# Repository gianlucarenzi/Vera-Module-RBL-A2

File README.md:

# VERA Module RBL-A2

<div align="center">

**Commander X16 graphics and sound, 256 KB of RAM disk, one Apple II slot.**

*🌐 English | [🌐 Italiano](#vera-module-rbl-a2-italiano)*

</div>

> [!WARNING]
> **v1.0 — PRE-PRODUCTION.** The PCB is routed and passes KiCad's DRC; the first boards are
> being made and are not tested yet. The firmware has been checked on the host and in an
> emulator only.

## ✨ Highlights

- 🎨 **VERA**, the Commander X16 video and audio chip, on a Lattice iCE40UP5K FPGA: two layers,
  128 sprites, 256 colours from 4096, VGA 640×480, PSG and PCM audio, SD card.
- 💾 **256 KB of expanded memory compatible with the Apple II Memory Expansion Card ("Slinky")**,
  with a ProDOS slot ROM: ProDOS sees the RAM disk `/SLINKY` at boot, no driver to load.
- ⚡ An **ESP32-S3FN8** at 240 MHz runs the slot bus in software: Slinky registers, slot ROM,
  VERA chip select.
- 🔌 **USB-C** for the ESP32 firmware (CH340C, auto-reset), **J6** to write the FPGA flash with `iceprog`.
- 📐 Full-size card drawn to **Apple IIgs Tech Note #28** (slots 1-3, fits the IIe):
  7.00" × 2.75", 4 layers.

## 🎮 What it can look like

What a game can look like on the VERA (320×240, 256 colours). These are **illustrative mock-ups
of two original demo games, not captures from the board**; `tools/make_demo_shots.py` draws them.

<div align="center">

*IRONHOLD (side-scrolling action) and CIRCUIT RUNNER (maze chase)*
</div>

## 🗺️ Memory map (slot n)

| Range | Function |
|---|---|
| `$C0n0-$C0n3` | Slinky: address bits 0-7 / 8-15 / 16-23 (`$C0n2` reads OR `$F0`), data with auto-increment |
| `$C0n4-$C0nE` | plain registers |
| `$C0nF` | bit 0 = 1: VERA registers at `$Cn00-$Cn1F`; 0: slot ROM (cleared by reset) |
| `$Cn00-$CnFF` | ProDOS slot ROM (block device, driver at `$Cn33`, `"VERAS"` at `$CnF0`) |
| `$Cn00-$Cn1F` | VERA registers, with `$C0nF` bit 0 = 1 |

After a reset the slot ROM is visible, so ProDOS finds the RAM disk. Programs show the VERA with
`$C0nF = 1`: libvera's start-up code and `vera_detect()` do it when they read `"VERAS"` at
`$CnF0`. Details: [A2-SLINKY.md](A2-SLINKY.md).

## 🔧 Hardware

| Block | Part |
|---|---|
| VERA FPGA | Lattice iCE40UP5K-SG48ITR, 25 MHz oscillator, SPI flash W25Q16 |
| Bus controller | ESP32-S3FN8 (240 MHz, 8 MB flash), 40 MHz crystal |
| Slot interface | 74LVC4245A level shifters on address, data and control |
| Audio | WM8524 I2S DAC, 3.5 mm jack |
| Video | VGA through the 2×8 header to the backplate adapter |
| USB | USB-C, CH340C USB-serial (internal clock), DTR/RTS auto-reset of the ESP32 |
| Storage | microSD |
| Power | 5 V from the slot; AMS1117 3.3 V and 1.2 V |
| PCB | 4 layers (F.Cu, 3V3 plane, GND plane, B.Cu), 177.8 × 69.85 mm |

<div align="center">

</div>

## 🏭 From KiCad to JLCPCB

```bash
./check_jlcpcb_stock.sh -n 5   # every BOM part in the JLCPCB library, with stock for 5 boards
./output_job.sh 1.0            # BOM, CPL, Gerbers, drill, iBOM, PDF, STEP/VRML, JLCPCB zip
```

- The BOM XML comes straight from the KiCad 5 schematic (`utilities/kicadcli`): it stops on a part
  without annotation or with a duplicated reference.
- **U11 WM8524** (C146242) is short at JLCPCB: it is listed in `jlcpcb-global-sourcing.txt`;
  choose **Global Sourcing** for that row when ordering.
- The board was routed from scratch with **fastroute** (`tools/route_nolimits.sh`): the result,
  reports and logs are in [routing/](routing/README.md).

Step by step, in Italian: [WORKFLOW.md](WORKFLOW.md) ([PDF](WORKFLOW.pdf)).

## 🧠 FPGA programming (iceprog)

<div align="center">

</div>

The VERA bitstream lives in the SPI flash U10 (W25Q16); the FPGA loads it at power-up.
`iceprog` writes it through **J6** with an FTDI FT232H or FT2232H adapter (MPSSE):

| J6 pin | Signal | FT232H / FT2232H (channel A) |
|---|---|---|
| 1 | 5 V (JP1) or 3.3 V (JP3), solder jumper | not needed: leave it unconnected |
| 2 | CDONE | ADBUS6 |
| 3 | CRESET | ADBUS7 |
| 4 | MISO (flash DO) | ADBUS2 |
| 5 | MOSI (flash DI) | ADBUS1 |
| 6 | SCK | ADBUS0 |
| 7 | SS (flash /CS) | ADBUS4 |
| 8 | GND | GND |

1. Power the board (in the computer) and **stop the ESP32**: hold BOOT0 (SW3), press and release
   RESET (SW1), release BOOT0. In download mode its pins are inputs; running, the firmware drives
   CRESET (GPIO 38) high against iceprog.
2. **Close JP2** ("FPGA PROGRAMMING"): CDONE goes to GND, so U9 selects the flash and U8 takes
   the microSD off the SPI bus.
3. Write and verify the flash:
   ```bash
   sudo apt install fpga-icestorm      # iceprog
   iceprog -t                          # reads the flash ID (W25Q16: ef 40 15)
   iceprog vera_module.bin             # erase, write, verify (the bitstream is not provided)
   iceprog -c vera_module.bin          # verify only
   ```
   With JP2 closed iceprog reports `cdone: low`: that is expected.
4. **Open JP2** and press RESET (SW1): the ESP32 firmware pulses CRESET, the FPGA loads the new
   bitstream and CDONE goes high (the "VERA READY" LED lights up).

## 💻 Firmware

`firmware/MCU` (PlatformIO, ESP32-S3) and the 6502 slot ROM (`firmware/MCU/6502`, cc65):

```bash
cd firmware/MCU
pio run                      # build (the slot ROM is assembled first)
pio run --target upload      # through the USB-C port (CH340C)
```

Host test: `firmware/MCU/test/host/test_a2_slinky.c`. Emulator: **a2emu-vera** with
`A2_VERA_CARD=rbl`. See [firmware/MCU/README.md](firmware/MCU/README.md).

## 📁 Repository

```
Vera-Module-RBL-A2/
├── README.md               # this file
├── A2-SLINKY.md            # Slinky memory, slot ROM, bus interface, tests
├── PIN-MAPPING.md          # ESP32-S3 pins
├── WORKFLOW.md / .pdf      # KiCad workflow, schematic to JLCPCB order (Italian)
├── VERA-MODULE-RBL.*       # KiCad 5 project: schematic and PCB
├── routing/                # fastroute result, reports and logs
├── firmware/MCU/           # ESP32-S3 firmware and 6502 slot ROM
├── docs/                   # Apple card guidelines (Tech Note #28) and links
├── images/                 # renders, demo mock-ups (images/demo)
├── tools/, *.py, *.sh      # routing, KiCad and JLCPCB production scripts
└── patches/, utilities/    # eeplot patches, kicadcli, STEP → WRL
```

## 📄 License

GNU General Public License v3.0, see [LICENSE](LICENSE). VERA comes from the
[Commander X16](https://www.commanderx16.com/) project.

---

# VERA Module RBL-A2 (Italiano)

<div align="center">

**La grafica e il suono del Commander X16, 256 KB di RAM disk, uno slot dell'Apple II.**

</div>

> [!WARNING]
> **v1.0 — PRE-PRODUZIONE.** Il PCB è sbrogliato e passa il DRC di KiCad; le prime schede sono in
> produzione e non sono ancora collaudate. Il firmware è stato verificato solo sull'host e in
> emulatore.

## ✨ In breve

- 🎨 **VERA**, il chip video e audio del Commander X16, su FPGA Lattice iCE40UP5K: due layer,
  128 sprite, 256 colori su 4096, VGA 640×480, audio PSG e PCM, scheda SD.
- 💾 **256 KB di memoria espansa compatibile con la Apple II Memory Expansion Card ("Slinky")**,
  con ROM di slot ProDOS: al boot ProDOS vede il RAM disk `/SLINKY`, senza driver da caricare.
- ⚡ Un **ESP32-S3FN8** a 240 MHz gestisce il bus dello slot via software: registri Slinky, ROM di
  slot, chip select della VERA.
- 🔌 **USB-C** per il firmware dell'ESP32 (CH340C, reset automatico), **J6** per scrivere la flash
  dell'FPGA con `iceprog`.
- 📐 Scheda a tutta lunghezza secondo l'**Apple IIgs Tech Note #28** (slot 1-3, va bene anche per
  il IIe): 7,00" × 2,75", 4 layer.

## 🎮 Come potrebbe apparire

Come può apparire un gioco sulla VERA (320×240, 256 colori). Sono **immagini dimostrative di due
giochi originali, non catture dalla scheda**; le disegna `tools/make_demo_shots.py`.

<div align="center">

</div>

## 🗺️ Mappa della memoria (slot n)

| Indirizzi | Funzione |
|---|---|
| `$C0n0-$C0n3` | Slinky: bit 0-7 / 8-15 / 16-23 dell'indirizzo (`$C0n2` letto OR `$F0`), dato con autoincremento |
| `$C0n4-$C0nE` | registri semplici |
| `$C0nF` | bit 0 = 1: registri VERA in `$Cn00-$Cn1F`; 0: ROM di slot (azzerato dal reset) |
| `$Cn00-$CnFF` | ROM di slot ProDOS (dispositivo a blocchi, driver a `$Cn33`, `"VERAS"` a `$CnF0`) |
| `$Cn00-$Cn1F` | registri VERA, con `$C0nF` bit 0 = 1 |

Dopo un reset è visibile la ROM, così ProDOS trova il RAM disk. I programmi mostrano la VERA con
`$C0nF = 1`: lo fanno il codice d'avvio di libvera e `vera_detect()` quando leggono `"VERAS"` in
`$CnF0`. Dettagli: [A2-SLINKY.md](A2-SLINKY.md).

## 🔧 Hardware

| Blocco | Parte |
|---|---|
| FPGA VERA | Lattice iCE40UP5K-SG48ITR, oscillatore 25 MHz, flash SPI W25Q16 |
| Controller di bus | ESP32-S3FN8 (240 MHz, 8 MB di flash), quarzo 40 MHz |
| Interfaccia slot | traslatori 74LVC4245A su indirizzi, dati e controlli |
| Audio | DAC I2S WM8524, jack 3,5 mm |
| Video | VGA tramite il connettore 2×8 verso l'adattatore sulla staffa |
| USB | USB-C, CH340C USB-seriale (clock interno), reset automatico dell'ESP32 con DTR/RTS |
| Memoria | microSD |
| Alimentazione | 5 V dallo slot; AMS1117 da 3,3 V e 1,2 V |
| PCB | 4 layer (F.Cu, piano 3V3, piano GND, B.Cu), 177,8 × 69,85 mm |

## 🏭 Da KiCad a JLCPCB

```bash
./check_jlcpcb_stock.sh -n 5   # ogni parte della BOM nella libreria JLCPCB, stock per 5 schede
./output_job.sh 1.0            # BOM, CPL, Gerber, forature, iBOM, PDF, STEP/VRML, zip JLCPCB
```

- L'XML della BOM viene direttamente dallo schema KiCad 5 (`utilities/kicadcli`): si ferma su un
  componente non annotato o con riferimento duplicato.
- **U11 WM8524** (C146242) scarseggia da JLCPCB: è in `jlcpcb-global-sourcing.txt`; nell'ordine si
  sceglie **Global Sourcing** per quella riga.
- La scheda è stata sbrogliata da zero con **fastroute** (`tools/route_nolimits.sh`): risultato,
  report e log sono in [routing/](routing/README.md).

Passo per passo: [WORKFLOW.md](WORKFLOW.md) ([PDF](WORKFLOW.pdf)).

## 🧠 Programmazione dell'FPGA (iceprog)

<div align="center">

</div>

Il bitstream della VERA sta nella flash SPI U10 (W25Q16); l'FPGA lo carica all'accensione.
`iceprog` lo scrive tramite **J6** con un adattatore FTDI FT232H o FT2232H (MPSSE):

| Pin J6 | Segnale | FT232H / FT2232H (canale A) |
|---|---|---|
| 1 | 5 V (JP1) o 3,3 V (JP3), ponticello a saldare | non serve: lasciarlo scollegato |
| 2 | CDONE | ADBUS6 |
| 3 | CRESET | ADBUS7 |
| 4 | MISO (DO della flash) | ADBUS2 |
| 5 | MOSI (DI della flash) | ADBUS1 |
| 6 | SCK | ADBUS0 |
| 7 | SS (/CS della flash) | ADBUS4 |
| 8 | GND | GND |

1. Alimentare la scheda (nel computer) e **fermare l'ESP32**: tenere premuto BOOT0 (SW3),
   premere e rilasciare RESET (SW1), rilasciare BOOT0. In download mode i suoi pin sono ingressi;
   se gira, il firmware tiene CRESET (GPIO 38) alto contro iceprog.
2. **Chiudere JP2** ("FPGA PROGRAMMING"): CDONE va a GND, così U9 seleziona la flash e U8 stacca
   la microSD dal bus SPI.
3. Scrivere e verificare la flash:
   ```bash
   sudo apt install fpga-icestorm      # iceprog
   iceprog -t                          # legge l'ID della flash (W25Q16: ef 40 15)
   iceprog vera_module.bin             # cancella, scrive, verifica (il bitstream non è fornito)
   iceprog -c vera_module.bin          # solo verifica
   ```
   Con JP2 chiuso iceprog segnala `cdone: low`: è normale.
4. **Aprire JP2** e premere RESET (SW1): il firmware dell'ESP32 dà l'impulso su CRESET, l'FPGA
   carica il nuovo bitstream e CDONE va alto (si accende il LED "VERA READY").

## 💻 Firmware

`firmware/MCU` (PlatformIO, ESP32-S3) e la ROM di slot 6502 (`firmware/MCU/6502`, cc65):

```bash
cd firmware/MCU
pio run                      # compila (prima assembla la ROM di slot)
pio run --target upload      # dalla porta USB-C (CH340C)
```

Test host: `firmware/MCU/test/host/test_a2_slinky.c`. Emulatore: **a2emu-vera** con
`A2_VERA_CARD=rbl`. Vedi [firmware/MCU/README.md](firmware/MCU/README.md).

## 📄 Licenza

GNU General Public License v3.0, vedi [LICENSE](LICENSE). La VERA viene dal progetto
[Commander X16](https://www.commanderx16.com/).

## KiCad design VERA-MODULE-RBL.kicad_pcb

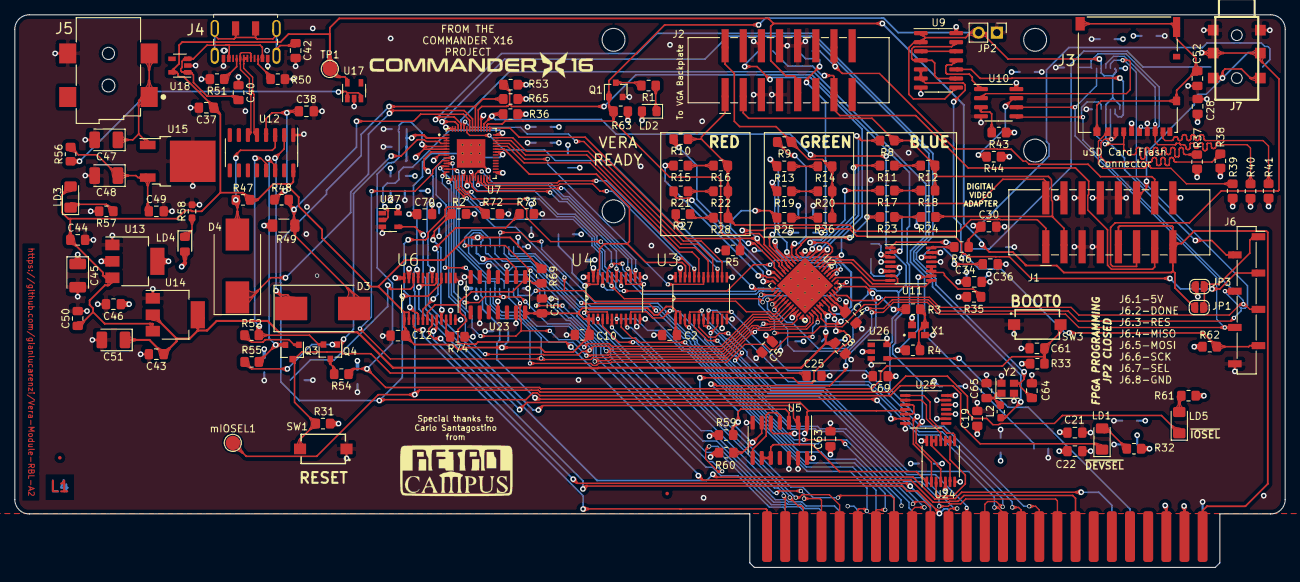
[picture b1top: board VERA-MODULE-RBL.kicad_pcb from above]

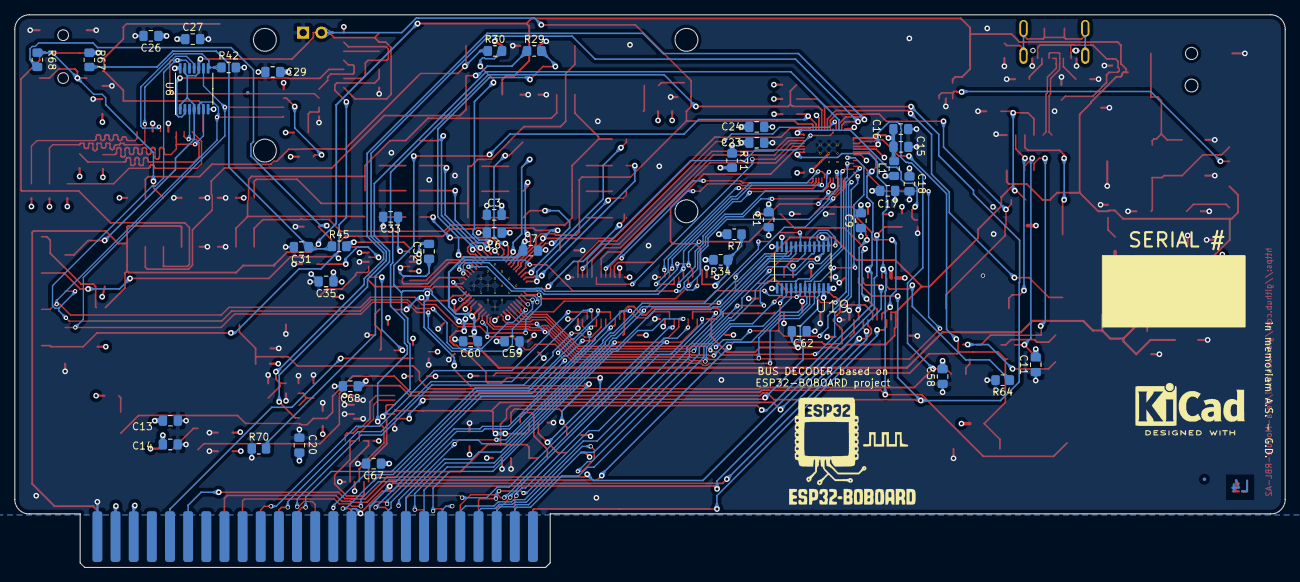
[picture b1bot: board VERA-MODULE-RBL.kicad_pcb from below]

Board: 4 copper layers, 177.8 x 77.3 mm, 199 parts (47 on the bottom side), 181 nets.

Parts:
C1, C2, C9, C10, C11, C12, C14, C16, C18, C20, C22, C23, C27, C28, C29, C38, C40, C42, C44, C46, C49, C50, C52, C57, C58, C61, C62, C63, C67, C68, C69, C70: 100nF; C_0805_2012Metric_Pad1.18x1.45mm_HandSolder
C3, C4, C5, C6, C7, C8, C25, C30, C31, C32, C33, C43, C59, C60: 1uF; C_0805_2012Metric_Pad1.18x1.45mm_HandSolder
C13, C15, C17, C19, C21, C24: 10uF; C_0805_2012Metric_Pad1.18x1.45mm_HandSolder
C26, C34, C35: 4.7uF; C_0805_2012Metric_Pad1.18x1.45mm_HandSolder
C36: 2.2uF; C_0805_2012Metric_Pad1.18x1.45mm_HandSolder
C37: 22uF; C_0805_2012Metric_Pad1.18x1.45mm_HandSolder
C45, C48, C51: 10uF-20V; CP_EIA-3528-12_Kemet-T_Pad1.50x2.35mm_HandSolder
C47: 10uF-35V; CP_EIA-3528-12_Kemet-T_Pad1.50x2.35mm_HandSolder
C64, C65: 27pF; C_0805_2012Metric_Pad1.18x1.45mm_HandSolder
D3, D4: DIOSCH20V; D_SMC_Handsoldering
FID1, FID2, FID3, FID4: Fiducial; Fiducial_0.5mm_Mask1mm
H1, H2, H3, H4: MountingHole; MountingHole_3.2mm_M3
J1, J2: CONN_SMD_HEADER_BOX_02x08_HX-JN2.54; IDC-Header_2x08_P2.54mm_Vertical_SMD
J3: CONN_DM3AT-SF-PEJM5; HRS_DM3AT-SF-PEJM5
J4: DX07S016JA1R1500; JAE_DX07S016JA1R1500
J5: PJ-002AH-SMT-TR; CUI_PJ-002AH-SMT-TR
J6: CONN_SMD_01x08_Staggered_2.54mm; PinSocket_1x08_P2.54mm_Vertical_SMD_Pin1Right
J7: PJ-313D; jack_3.5_pj313d-smt
J8: Bus_Apple_II_Card_Side; APPLE2-PERIPHERAL-BUS-EDGE
JP1, JP3: SolderJumper_2_Open; SolderJumper-2_P1.3mm_Open_RoundedPad1.0x1.5mm
JP2: Jumper_2_Open; PinHeader_1x02_P2.54mm_Vertical
L1: FB0805100R100MHZ4A; L_0805_2012Metric_Pad1.15x1.40mm_HandSolder
L2: IND0603600R100MHZ300mA; L_0603_1608Metric_Pad1.05x0.95mm_HandSolder
LBL1: Label-20mmx10mm; Label-20mmx10mm-Silkscreen
LD1, LD3, LD5: RED; LED_1206_3216Metric_Pad1.42x1.75mm_HandSolder
LD2, LD4: GREEN; LED_0805_2012Metric_Pad1.15x1.40mm_HandSolder
LOGO1: VERA X16 LOGO; x16logo
LOGO2: RETROCAMPUS; retrocampus_silkscreen_16.9mm_8.3mm
LOGO3: KiCAD DESIGN; KiCad-Logo2_6mm_SilkScreen
LOGO5: ESP32_BOBOARD; ESP32_BOBOARD_5V_21.7mmx21.7mm
Q1: MOSFET-BSS138-SOT-23; SOT-23
Q3, Q4: BC817,SOT-23; SOT-23
R1: 2K7; R_0805_2012Metric_Pad1.20x1.40mm_HandSolder
R2, R35, R56, R64, R72, R73, R74: CREZ08051%; R_0805_2012Metric_Pad1.20x1.40mm_HandSolder
R3, R4: 50R; R_0805_2012Metric_Pad1.20x1.40mm_HandSolder
R5, R7, R34, R36, R47, R48, R53, R62, R63, R65, R69, R70, R71: 10K; R_0805_2012Metric_Pad1.20x1.40mm_HandSolder
R8, R9, R10: 4K3; R_0805_2012Metric_Pad1.20x1.40mm_HandSolder
R11, R13, R15: 2K; R_0805_2012Metric_Pad1.20x1.40mm_HandSolder
R12, R14, R16: 150R; R_0805_2012Metric_Pad1.20x1.40mm_HandSolder
R17, R19, R21: 910R; R_0805_2012Metric_Pad1.20x1.40mm_HandSolder
R18, R20, R22: 160R; R_0805_2012Metric_Pad1.20x1.40mm_HandSolder
R23, R25, R27, R57: 510R; R_0805_2012Metric_Pad1.20x1.40mm_HandSolder
R24, R26, R28: 27R; R_0805_2012Metric_Pad1.20x1.40mm_HandSolder
R29, R30: 820R; R_0805_2012Metric_Pad1.20x1.40mm_HandSolder
R31, R33, R59, R60: 4K7; R_0805_2012Metric_Pad1.20x1.40mm_HandSolder
R32, R61: 330R; R_0805_2012Metric_Pad1.20x1.40mm_HandSolder
R37, R38, R39, R40, R41, R42, R43, R44: 47K; R_0805_2012Metric_Pad1.20x1.40mm_HandSolder
R45, R46, R67, R68: 560R; R_0805_2012Metric_Pad1.20x1.40mm_HandSolder
R49: DNP; R_1206_3216Metric_Pad1.30x1.75mm_HandSolder
R50, R51: 5K1; R_0805_2012Metric_Pad1.20x1.40mm_HandSolder
R52, R55: 2K2; R_0805_2012Metric_Pad1.20x1.40mm_HandSolder
R54: 220R; R_0805_2012Metric_Pad1.20x1.40mm_HandSolder
R58: 330R; R_0603_1608Metric_Pad0.98x0.95mm_HandSolder
SW1, SW3: SPST2P; SPST-7.3x3.9x2.5-WUERTH-434121025816
TP1: TP5V; TestPoint_Pad_D2.0mm
U2: ICE40UP5K-SG48ITR; QFN-48-1EP_7x7mm_P0.5mm_EP5.6x5.6mm
U3, U4, U6, U19: 74LVC4245APW_118; IC_74LVC4245_SOP65P640X110-24N
U5: IC74HC00; SOIC-14_3.9x8.7mm_P1.27mm
U7: ESP32-S3FN8; IC_ESP32-S3FN8-QFN40P700X700X90-57N
U8: 74CBTLV3126PW,118; TSSOP-14_4.4x5mm_P0.65mm
U9: CD4011B; SOIC-14_3.9x8.7mm_P1.27mm
U10: W25Q16JVSNIQ; SOIC-8_3.9x4.9mm_P1.27mm
U11: WM8524CGEDT; TSSOP-16_4.4x5mm_P0.65mm
U12: USBCH340C; SOIC-16_3.9x9.9mm_P1.27mm
U13: AMS1117-3.3; SOT-223-3_TabPin2
U14: AMS1117-1.2; SOT-223-3_TabPin2
U15: L7805; TO-252-2
U17, U18: MAX40200AUK; SOT-23-5
U23: SN74HCT04DR; SOIC-14_3.9x8.7mm_P1.27mm
U24, U25: SN74LVC00; TSSOP-14_4.4x5mm_P0.65mm
U26, U27: SN74LVC1G07DBVR; SOT-23-5
X1: OT3EL89CJI-111YLC-25M; OSC_ECS-2033-250-BN
Y2: 40.000Mhz; Crystal_SMD_2520-4Pin_2.5x2.0mm
mIOSEL1: TestPoint; TestPoint_Pad_D2.0mm

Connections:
1V2: C7.1, C8.1, C43.1, C51.1, C60.1, U2.5, U2.29, U2.30, U14.2
3V3: C1.2, C3.2, C4.1, C5.1, C6.1, C9.2, C11.2, C13.1, C14.1, C17.1, C18.1, C19.1, C20.1, C21.1, C22.1, C23.2, C24.2, C26.1, C27.1, C28.1, C29.1, C34.1, C35.1, C45.1, C46.1, C58.2, C59.2, C63.2, C67.1, C68.1, C69.1, C70.1, J1.4, J1.16, J3.4, JP3.1, L1.1, LD2.2, LD4.2, R7.2, R31.1, R32.1, R33.1, R34.2, R35.1, R36.2, R37.1, R38.1, R39.1, R40.1, R41.1, R43.1, R44.1, R49.2, R53.2, R59.2, R60.1, R61.1, R62.1, R63.1, R65.2, R71.1, U2.1, U2.22, U2.24, U2.33, U3.23, U3.24, U4.23, U4.24, U5.14, U6.23, U6.24, U7.20, U7.29, U7.46, U7.55, U7.56, U8.14, U9.14, U10.8, U11.6, U11.15, U13.2, U19.23, U19.24, U24.5, U24.14, U25.14, U26.5, U27.5, X1.4
5V: C2.2, C10.2, C12.2, C37.1, C44.1, C50.1, C57.1, C62.2, J1.9, J1.15, J2.9, J8.25, JP1.1, LD3.2, R47.2, R69.1, TP1.1, U3.1, U3.2, U4.1, U4.2, U6.1, U6.2, U12.16, U13.3, U14.3, U17.5, U18.5, U19.1, U23.14
/BusDecoder/B: U25.3, U25.5
/BusDecoder/VDD3P3: C15.1, C16.1, L1.2, U7.2, U7.3
/BusDecoder/a1: U24.8, U25.1
/BusDecoder/a2: U24.11, U25.2
/BusDecoder/n1: U24.3, U24.9, U24.10
/BusDecoder/n2: U24.6, U24.12, U24.13
/PowerSupply/D+: J4.6, J4.7, U12.5
/PowerSupply/D-: J4.5, J4.8, U12.6
/Vera FPGA flash/CLK: J3.5, R42.1, U8.8
/Vera FPGA flash/CMD: J3.3, R37.2, U8.6
/Vera FPGA flash/DAT0: J3.7, R40.2, U8.11
/Vera FPGA flash/DAT1: J3.8, R41.2
/Vera FPGA flash/DAT2: J3.1, R39.2
/Vera FPGA flash/DAT3: J3.2, R38.2, U8.3
/Vera FPGA flash/FLASH_SSEL_N: U9.11, U10.1
/Vera FPGA flash/SD_SSEL_N: U8.2, U9.10
A0: J8.2, U4.3
A1: J8.3, U4.4
A2: J8.4, U4.5
A3: J8.5, U4.6
A4: J8.6, U4.7
A5: J8.7, U4.8
A6: J8.8, U4.9
A7: J8.9, U4.10
A8: J8.10, U3.3
A9: J8.11, U3.4
A10: J8.12, U3.5
A11: J8.13, U3.6
A12: J8.14, U3.7
A13: J8.15, U3.8
A14: J8.16, U3.9
A15: J8.17, U3.10
ASYSCLK: R4.1, U11.10
AUD1L: J1.11, J7.3, R67.1
AUD1R: J1.12, J7.2, R68.1
AUDIO_BCK: U2.38, U11.9
AUDIO_DATA: U2.42, U11.7
AUDIO_LRCK: U2.43, U11.8
BOOT0: C61.1, R33.2, R54.1, SW3.2, U7.5
D0: J8.49, U19.3
D1: J8.48, U19.4
D2: J8.47, U19.5
D3: J8.46, U19.6
D4: J8.45, U19.7
D5: J8.44, U19.8
D6: J8.43, U19.9
D7: J8.42, U19.10
ESP32_CH340_RXD: D3.2, R48.2, R49.1, U7.50
ESP32_CH340_TXD: D4.1, U7.49
FPGA_CDONE: J6.2, JP2.2, Q1.1, R63.2, U2.7, U7.44, U8.1, U8.4, U8.10, U8.13, U9.1, U9.2, U9.8
GND: C1.1, C2.1, C3.1, C4.2, C5.2, C6.2, C7.2, C8.2, C9.1, C10.1, C11.1, C12.1, C13.2, C14.2, C15.2, C16.2, C17.2, C18.2, C19.2, C20.2, C21.2, C22.2, C23.1, C24.1, C25.2, C26.2, C27.2, C28.2, C29.2, C30.2, C31.2, C33.2, C34.2, C35.2, C36.2, C37.2, C38.2, C40.2, C42.2, C43.2, C44.2, C45.2, C46.2, C47.2, C48.2, C49.2, C50.2, C51.2, C52.2, C57.2, C58.1, C59.1, C60.2, C61.2, C62.1, C63.1, C64.1, C65.1, C67.2, C68.2, C69.2, C70.2, J1.5, J1.6, J1.7, J1.8, J1.10, J2.5, J2.6, J2.7, J2.8, J2.10, J3.6, J4.1, J4.12, J5.2, J6.8, J7.1, J8.26, JP2.1, Q1.2, R2.2, R5.1, R42.2, R50.2, R51.2, R57.2, R58.2, R64.2, R70.1, R72.2, R73.2, R74.2, SW1.1, SW3.1, U2.49, U3.11, U3.12, U3.13, U4.11, U4.12, U4.13, U5.7, U5.12, U5.13, U6.11, U6.12, U6.13, U7.57, U8.7, U9.7, U10.4, U11.4, U11.13, U12.1, U13.1, U14.1, U15.2, U17.2, U18.2, U19.11, U19.12, U19.13, U23.3, U23.5, U23.7, U23.9, U23.11, U23.13, U24.7, U25.7, U25.9, U25.10, U25.12, U25.13, U26.3, U27.3, X1.2, Y2.2, Y2.4
unnamed: C30.1, R46.1, R68.2
unnamed: C31.1, R45.1, R67.2
unnamed: C32.1, U11.5
unnamed: C32.2, U11.3
unnamed: C33.1, U11.2
unnamed: C36.1, U11.14
unnamed: C38.1, R48.1, U12.4
unnamed: C40.1, J4.2, J4.11, U18.1, U18.3
unnamed: C42.1, J4.S1, J4.S2, J4.S3, J4.S4, J4.S5, J4.S6
unnamed: C47.1, J5.1A, J5.1B, U15.1
unnamed: C48.1, C49.1, R56.2, U15.3
unnamed: C52.1, J3.SH
unnamed: C64.2, U7.53, Y2.3
unnamed: C65.2, L2.2, Y2.1
unnamed: D3.1, U12.2
unnamed: D4.2, R47.1, U12.3
unnamed: J4.3, R50.1
unnamed: J4.9, R51.1
unnamed: J6.1, JP1.2, JP3.2
unnamed: J8.23, J8.28
unnamed: J8.24, J8.27
unnamed: L2.1, U7.54
unnamed: LD1.2, R32.2
unnamed: LD2.1, R1.1
unnamed: LD3.1, R57.1
unnamed: LD4.1, R58.1
unnamed: LD5.2, R61.2
unnamed: Q1.3, R1.2
unnamed: Q3.1, R52.1
unnamed: Q3.2, R55.2, U12.14
unnamed: Q4.1, R55.1
unnamed: Q4.2, R52.2, U12.13
unnamed: Q4.3, R54.2
unnamed: R2.1, U6.9
unnamed: R3.2, R4.2, X1.3
unnamed: R11.1, R12.2
unnamed: R13.1, R14.2
unnamed: R15.1, R16.2
unnamed: R17.1, R18.2
unnamed: R19.1, R20.2
unnamed: R21.1, R22.2
unnamed: R23.1, R24.2
unnamed: R25.1, R26.2
unnamed: R27.1, R28.2
unnamed: R35.2, U11.11, U11.12
unnamed: R43.2, U10.3
unnamed: R44.2, U10.7
unnamed: R45.2, U11.1
unnamed: R46.2, U11.16
unnamed: R56.1, U17.1, U17.3
unnamed: R64.1, U6.22
unnamed: R71.2, U7.8
unnamed: R72.1, U6.4
unnamed: R73.1, U6.5
unnamed: R74.1, U6.10
unnamed: U5.4, U5.8
unnamed: U9.3, U9.12
unnamed: U9.4, U9.9, U9.13
unnamed: U19.2, U23.2
PHI0: J8.40, U6.7
RST\EN: C25.1, Q3.3, R31.2, SW1.2, U7.4
R~W: J8.18, R69.2, U6.6, U23.1
SPI_MISO: J6.4, U2.17, U8.12, U10.2
SPI_MOSI: J6.5, U2.14, U8.5, U10.5
SPI_SCK: J6.6, U2.15, U8.9, U10.6
SPI_SSEL_N: J6.7, R62.2, U2.16, U9.5, U9.6
VGABLUE: J1.3, J2.3, R8.1, R12.1, R18.1, R24.1
VGAGREEN: J1.2, J2.2, R9.1, R14.1, R20.1, R26.1
VGAHSYNC: J1.13, J2.13, R29.1
VGARED: J1.1, J2.1, R10.1, R16.1, R22.1, R28.1
VGAVSYNC: J1.14, J2.14, R30.1
VGA_B0: R8.2, U2.46
VGA_B1: R11.2, U2.47
VGA_B2: R17.2, U2.48
VGA_B3: R23.2, U2.2
VGA_G0: R9.2, U2.3
VGA_G1: R13.2, U2.4
VGA_G2: R19.2, U2.6
VGA_G3: R25.2, U2.9
VGA_HSYNC: R29.2, U2.44
VGA_R0: R10.2, U2.10
VGA_R1: R15.2, U2.11
VGA_R2: R21.2, U2.12
VGA_R3: R27.2, U2.13
VGA_VSYNC: R30.2, U2.45
VSYSCLK: R3.1, U2.35
mA0: U2.40, U4.21, U7.17
mA1: U2.39, U4.20, U7.18
mA2: U2.37, U4.19, U7.19
mA3: U2.41, U4.18, U7.21
mA4: U2.34, U4.17, U7.22
mA5: U4.16, U7.23
mA6: U4.15, U7.24
mA7: U4.14, U7.25
mA8: U3.21, U7.26
mA9: U3.20, U7.27
mA10: U3.19, U7.38
mA11: U3.18, U7.39
mA12: U3.17, U7.40
mA13: U3.16, U7.41
mA14: U3.15, U7.51
mA15: U3.14, U7.52
mD0: U2.27, U7.9, U19.21
mD1: U2.26, U7.10, U19.20
mD2: U2.25, U7.11, U19.19
mD3: U2.23, U7.12, U19.18
mD4: U2.21, U7.13, U19.17
mD5: U2.20, U7.14, U19.16
mD6: U2.19, U7.15, U19.15
mD7: U2.18, U7.16, U19.14
mPHI0: U5.1, U5.5, U6.17, U7.6, U25.4
mR~W: U5.2, U5.9, U5.10, U6.18, U7.7, U24.1
~ABUS_OE: R7.1, R34.1, U3.22, U4.22, U7.37
~DEVSEL: J8.41, U6.8
~FPGA_RESET: J6.3, R5.2, U2.8, U7.43
~IOSEL: J8.1, U6.3
~IRQ: J8.30, U26.4
~OE: U19.22, U25.6
~RES: J8.31, U27.4
~mCARD_RD: R53.1, U7.47, U24.4
~mDEVSEL: LD1.1, R65.1, U6.16, U7.48
~mIOSEL: LD5.1, U6.21, U7.36, mIOSEL1.1
~mRE: R59.1, U2.36, U5.3
~mRESET: R70.2, U7.42, U27.2
~mVCS0: R36.1, U2.28, U7.45, U24.2
~mVIRQ: U2.32, U26.2
~mWE: R60.2, U2.31, U5.6

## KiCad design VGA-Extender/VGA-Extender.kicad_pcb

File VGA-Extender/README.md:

# VGA-Extender for the VERA Module RBL-A2

<div align="center">

**The VGA output of the VERA Module RBL-A2, out of the Apple II case.**

*🌐 English | [🌐 Italiano](#vga-extender-per-il-vera-module-rbl-a2-italiano)*

</div>

## ✨ What it is

A small 2-layer board (44.1 × 33.8 mm) with a **VGA (HD15 female) connector**, to fix on a
rear slot bracket of the Apple II. It is linked to the **J2** 2×8 box header of the VERA Module
RBL-A2 with a **16-way IDC ribbon cable**: the card itself has no VGA connector, only the header.

| | |
|---|---|
| J1 | 2×8 SMD box header (HX JN2.54-2x8P, LCSC C41376031), to the card |
| J2 | VGA HD15 female, right angle (Connfly DS1038-15FBNSiA74-0CC, LCSC C75754, through-hole) |
| C1, C2 | 100 nF from each shield lug to GND (LCSC C28233) |
| cable | 16-way 1.27 mm grey ribbon with two IDC 2×8 sockets (e.g. Connfly DS1016-16MANBG, LCSC C7500469), crimped by hand |

## 🔌 Pinout

The header pins go straight to the VGA pins of the same number (1:1), as on J2 of the card:

| Pin | Signal | Pin | Signal |
|---|---|---|---|
| 1 | RED | 9 | +5 V |
| 2 | GREEN | 10 | GND |
| 3 | BLUE | 11, 12 | not connected |
| 4 | not connected | 13 | HSYNC |
| 5-8 | GND | 14 | VSYNC |
| | | 15, 16 | not connected (16: header only) |

The connector shell (S1, S2) goes to GND through C1 and C2.

<div align="center">

</div>

## 🏭 From KiCad to JLCPCB

The same scripts as the main project:

```bash
./check_jlcpcb_stock.sh -n 5   # every BOM part in the JLCPCB library, with stock for 5 boards
./output_job.sh 1.0            # BOM, CPL, Gerbers, drill, iBOM, PDF, STEP/VRML, JLCPCB zip
```

The result is `VERA-VGA-Extender-A2-v1.0.zip` (Gerbers and drill from `production/`) with
`VERA-VGA-Extender-A2-v1.0-JLCPCB-BOM.csv` and `-CPL.csv`, the interactive BOM in
`ibom/ibom.html`, the schematic in `VGA-Extender.pdf` and the 3D models in `images/`. KiCad 5 comes
from the system when it is version 5, otherwise from the KiCad 5 AppImage (`kicad5`); see the
[WORKFLOW](../WORKFLOW.md) of the main project.

J2 is through-hole: JLCPCB solders it by hand with the Standard PCBA (a few cents a board). With
only three SMD parts the board can also be assembled by hand.

## 📄 License

GNU General Public License v3.0, see [LICENSE](../LICENSE).

---

# VGA-Extender per il VERA Module RBL-A2 (Italiano)

<div align="center">

**L'uscita VGA del VERA Module RBL-A2, fuori dal case dell'Apple II.**

</div>

## ✨ Cos'è

Una piccola scheda a 2 layer (44,1 × 33,8 mm) con un **connettore VGA (HD15 femmina)**, da fissare
su una staffa posteriore dell'Apple II. Si collega al connettore box 2×8 **J2** del VERA Module
RBL-A2 con un **cavo piatto IDC a 16 poli**: la scheda principale non ha il connettore VGA, solo il
connettore box.

| | |
|---|---|
| J1 | connettore box 2×8 SMD (HX JN2.54-2x8P, LCSC C41376031), verso la scheda |
| J2 | VGA HD15 femmina ad angolo retto (Connfly DS1038-15FBNSiA74-0CC, LCSC C75754, THT) |
| C1, C2 | 100 nF da ogni linguetta dello schermo a GND (LCSC C28233) |
| cavo | piattina grigia a 16 poli, passo 1,27 mm, con due connettori IDC 2×8 (per esempio Connfly DS1016-16MANBG, LCSC C7500469), crimpati a mano |

## 🔌 Piedinatura

I pin del connettore box vanno dritti ai pin VGA con lo stesso numero (1:1), come J2 della scheda:

| Pin | Segnale | Pin | Segnale |
|---|---|---|---|
| 1 | ROSSO | 9 | +5 V |
| 2 | VERDE | 10 | GND |
| 3 | BLU | 11, 12 | non collegati |
| 4 | non collegato | 13 | HSYNC |
| 5-8 | GND | 14 | VSYNC |
| | | 15, 16 | non collegati (il 16 c'è solo sul connettore box) |

Lo schermo del connettore (S1, S2) va a GND attraverso C1 e C2.

## 🏭 Da KiCad a JLCPCB

Gli stessi script del progetto principale:

```bash
./check_jlcpcb_stock.sh -n 5   # ogni parte della BOM nella libreria JLCPCB, stock per 5 schede
./output_job.sh 1.0            # BOM, CPL, Gerber, forature, iBOM, PDF, STEP/VRML, zip JLCPCB
```

Il risultato è `VERA-VGA-Extender-A2-v1.0.zip` (Gerber e forature da `production/`), con
`VERA-VGA-Extender-A2-v1.0-JLCPCB-BOM.csv` e `-CPL.csv`, la BOM interattiva in `ibom/ibom.html`,
lo schema in `VGA-Extender.pdf` e i modelli 3D in `images/`. KiCad 5 viene dal sistema se è la
versione 5, altrimenti dall'AppImage di KiCad 5 (`kicad5`); vedi il [WORKFLOW](../WORKFLOW.md) del
progetto principale.

J2 è THT: JLCPCB lo salda a mano con lo Standard PCBA (pochi centesimi a scheda). Con soli tre
componenti SMD la scheda si può anche montare a mano.

## 📄 Licenza

GNU General Public License v3.0, vedi [LICENSE](../LICENSE).

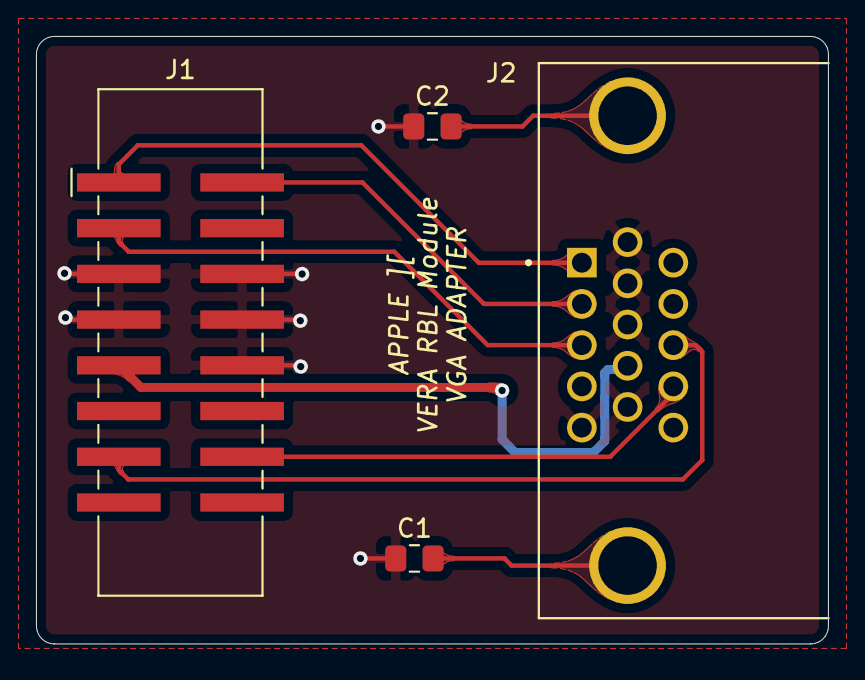
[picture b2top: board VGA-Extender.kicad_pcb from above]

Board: 2 copper layers, 44.0 x 33.8 mm, 5 parts (1 on the bottom side), 9 nets.

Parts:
C1, C2: 100nF; C_0805_2012Metric_Pad1.18x1.45mm_HandSolder
J1: CONN_SMD_HEADER_BOX_02x08_HX-JN2.54; IDC-Header_2x08_P2.54mm_Vertical_SMD
J2: DS1038-15FBNSiA74-0CC; CONNFLY_DS1038-15FBNSIA74-0CC
LOGO1: RETROCAMPUS; retrocampus_silkscreen_16.9mm_8.3mm

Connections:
+5V: J1.9, J2.9
GND: C1.1, C2.1, J1.5, J1.6, J1.7, J1.8, J1.10, J2.5, J2.6, J2.7, J2.8, J2.10
unnamed: C1.2, J2.S1
unnamed: C2.2, J2.S2
VGABLUE: J1.3, J2.3
VGAGREEN: J1.2, J2.2
VGAHSYNC: J1.13, J2.13
VGARED: J1.1, J2.1
VGAVSYNC: J1.14, J2.14

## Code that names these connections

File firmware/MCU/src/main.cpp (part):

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 * memory.
 *
 * Slot signals (PIN-MAPPING.md, A2-SLINKY.md):
 *   GPIO 1   PHI0       (slot pin 40)
 *   GPIO 41  CARD_RD_N: the card drives the data bus (data transceiver ~OE)
 *   GPIO 42  /DEVSEL input (slot pin 41)
 *   GPIO 48  /IOSEL  input (slot pin 1)
 *   GPIO 37  Apple /RESET (slot pin 31): must be open drain
 *
 * Style: Allman
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 * =========================================================================== */

/* --- Bank 0 Signals (GPIO 0-31) --- */
#define PIN_PHI0        1    /* Apple PHI0 (Pin 6) */
#define PIN_RW          2    /* Read/Write, High = Read (Pin 7) */

/* D0-D7: GPIO 4 to 11 (Pins 9-16, contiguous in Bank 0): D0 = GPIO 4 */
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#define PIN_CDONE       39   /* Vera Programmed Status Input (Pin 44) */
#define PIN_DEV_SEL_N   40   /* VERA chip select output (Pin 45, active LOW) */
#define PIN_CARD_RD_N   41   /* Card drives the data bus: data transceiver ~OE gating (Pin 47, active LOW) */
#define PIN_DEVSEL_N    42   /* Apple /DEVSEL input (Pin 48, active LOW) */
#define PIN_A14         45   /* Address Bit 14 (Pin 51) */
#define PIN_A15         46   /* Address Bit 15 (Pin 52) */
#define PIN_ABUS_OE_N   47   /* ~OE of the address translators (A0-A15), 10 kΩ pull-up (Pin 37, active LOW) */
#define PIN_IOSEL_N     48   /* Apple /IOSEL input (Pin 36, active LOW) */

/* Serial Debug (UART0 default pins on ESP32-S3 QFN56) */
#define PIN_UART_TX     43   /* UART0 TX (Pin 49) */
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 * =========================================================================== */
static void IRAM_ATTR MonitorTask(void *arg)
{
    static const int din_pins[]  = { PIN_PHI0, PIN_RW, PIN_IOSEL_N, PIN_DEVSEL_N };
    static const int dout_pins[] = { PIN_DEV_SEL_N, PIN_CARD_RD_N };
    dedic_gpio_bundle_handle_t din_bundle, dout_bundle;
    const dedic_gpio_bundle_config_t in_cfg =
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    cfg.pull_up_en   = GPIO_PULLUP_DISABLE;
    cfg.pull_down_en = GPIO_PULLDOWN_DISABLE;
    cfg.mode         = GPIO_MODE_INPUT;
    cfg.pin_bit_mask = (1ULL << PIN_PHI0) | (1ULL << PIN_RW) | DBUS_MASK |
                       (0x3FFULL << ABUS_LO_SHIFT);
    gpio_config(&cfg);
    cfg.pin_bit_mask = (1ULL << PIN_A10) | (1ULL << PIN_A11) |
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

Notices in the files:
README.md:
License: GPL v3
parts and their libraries:
From markadev/KiCad-AppleII 9c33c63 (CC BY-SA 4.0), converted to KiCad 5
